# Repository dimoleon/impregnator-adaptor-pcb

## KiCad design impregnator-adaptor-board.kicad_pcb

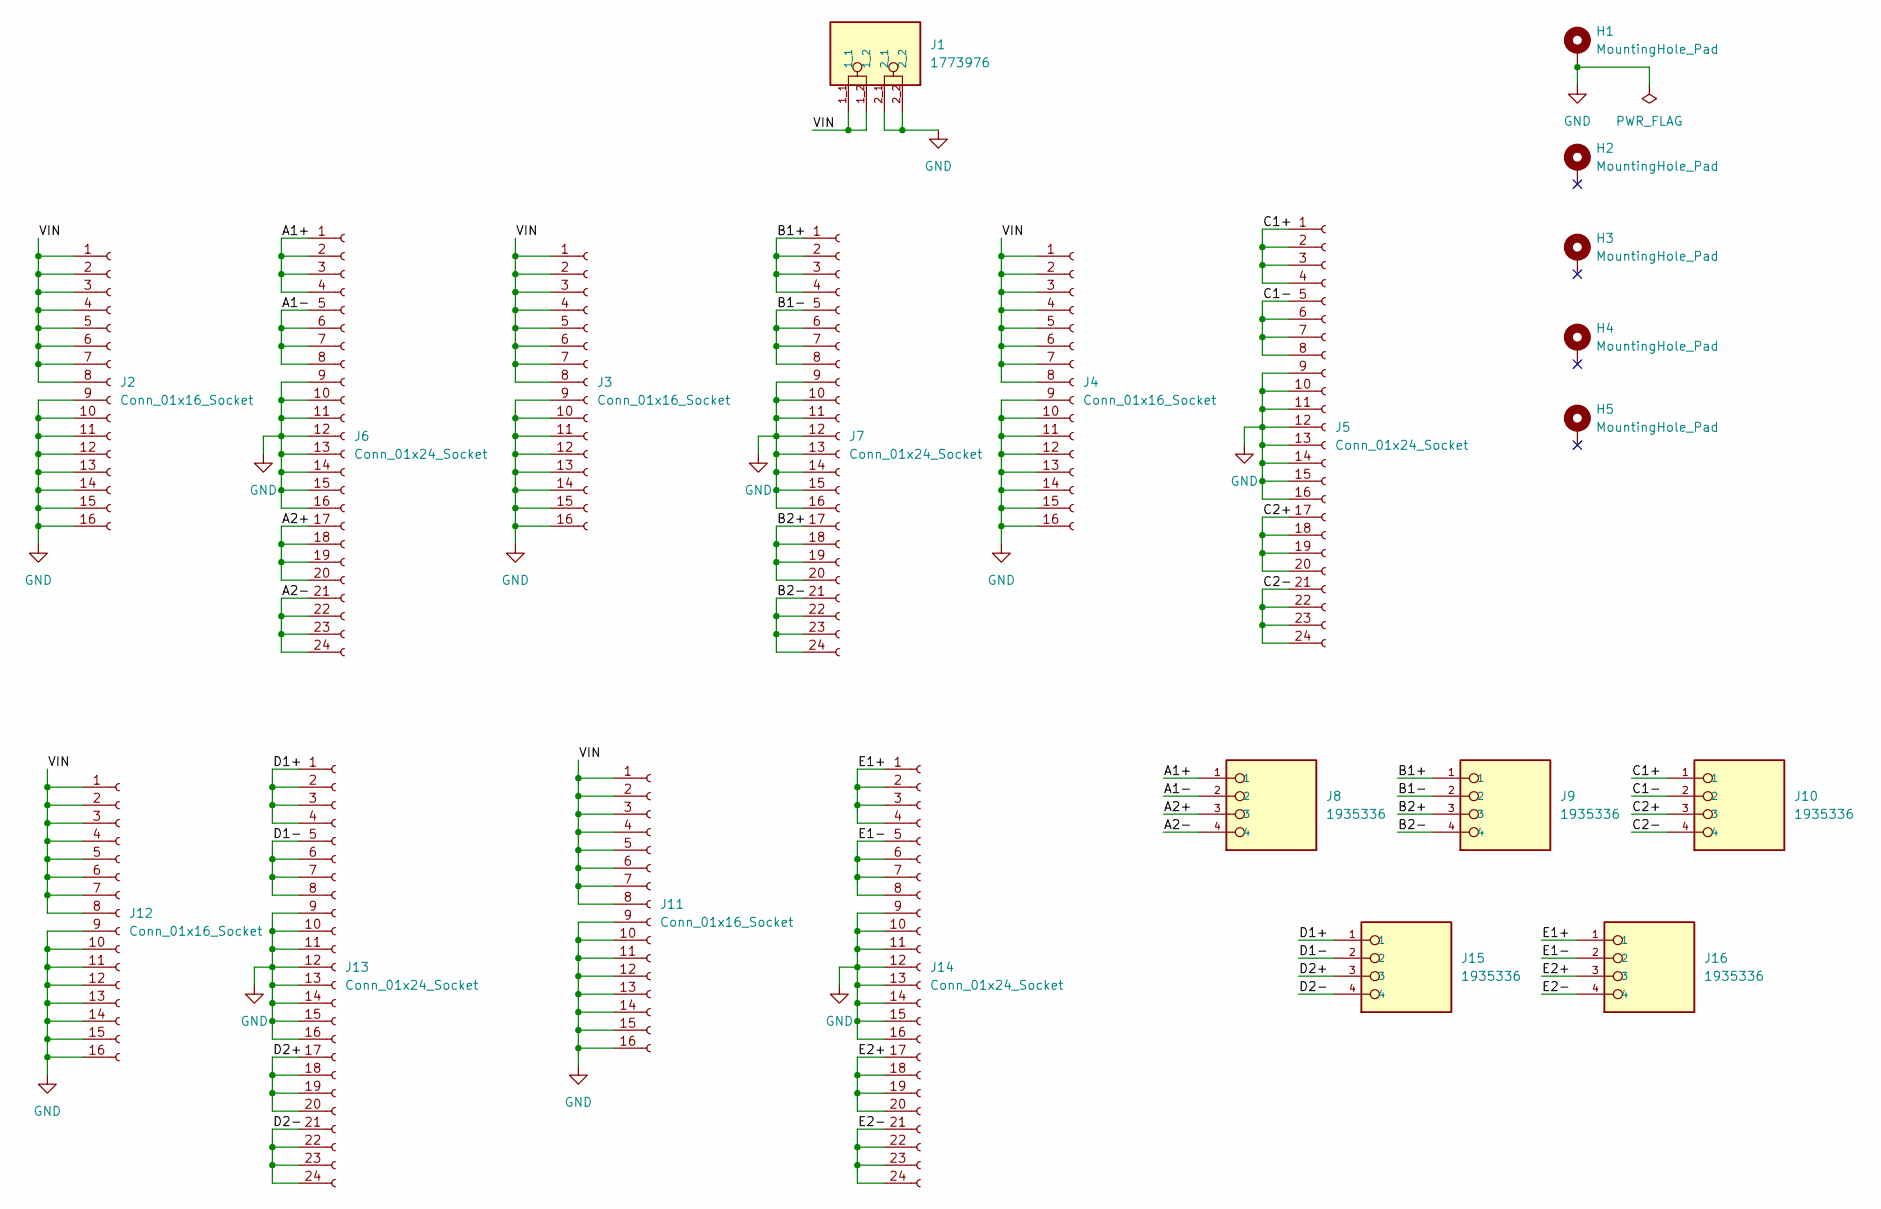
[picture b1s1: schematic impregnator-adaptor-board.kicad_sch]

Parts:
H1, H2, H3, H4, H5: MountingHole_Pad; MountingHole_3.2mm_M3_DIN965_Pad
J1: 1773976; PHOENIX_1773976; PARTREV 19.03.2015
J2, J3, J4, J11, J12: Conn_01x16_Socket; PinSocket_4x04_P2.54mm_Vertical
J5, J6, J7, J13, J14: Conn_01x24_Socket; PinSocket_2x12_P2.54mm_Vertical
J8, J9, J10, J15, J16: 1935336; PHOENIX_1935336

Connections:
/A1+: J6.1, J6.2, J6.3, J6.4, J8.1
/A1-: J6.5, J6.6, J6.7, J6.8, J8.2
/A2+: J6.17, J6.18, J6.19, J6.20, J8.3
/A2-: J6.21, J6.22, J6.23, J6.24, J8.4
/B1+: J7.1, J7.2, J7.3, J7.4, J9.1
/B1-: J7.5, J7.6, J7.7, J7.8, J9.2
/B2+: J7.17, J7.18, J7.19, J7.20, J9.3
/B2-: J7.21, J7.22, J7.23, J7.24, J9.4
/C1+: J5.1, J5.2, J5.3, J5.4, J10.1
/C1-: J5.5, J5.6, J5.7, J5.8, J10.2
/C2+: J5.17, J5.18, J5.19, J5.20, J10.3
/C2-: J5.21, J5.22, J5.23, J5.24, J10.4
/D1+: J13.1, J13.2, J13.3, J13.4, J15.1
/D1-: J13.5, J13.6, J13.7, J13.8, J15.2
/D2+: J13.17, J13.18, J13.19, J13.20, J15.3
/D2-: J13.21, J13.22, J13.23, J13.24, J15.4
/E1+: J14.1, J14.2, J14.3, J14.4, J16.1
/E1-: J14.5, J14.6, J14.7, J14.8, J16.2
/E2+: J14.17, J14.18, J14.19, J14.20, J16.3
/E2-: J14.21, J14.22, J14.23, J14.24, J16.4
/VIN: J1.1_1, J1.1_2, J2.1, J2.2, J2.3, J2.4, J2.5, J2.6, J2.7, J2.8, J3.1, J3.2, J3.3, J3.4, J3.5, J3.6, J3.7, J3.8, J4.1, J4.2, J4.3, J4.4, J4.5, J4.6, J4.7, J4.8, J11.1, J11.2, J11.3, J11.4, J11.5, J11.6, J11.7, J11.8, J12.1, J12.2, J12.3, J12.4, J12.5, J12.6, J12.7, J12.8
GND: H1.1, J1.2_1, J1.2_2, J2.9, J2.10, J2.11, J2.12, J2.13, J2.14, J2.15, J2.16, J3.9, J3.10, J3.11, J3.12, J3.13, J3.14, J3.15, J3.16, J4.9, J4.10, J4.11, J4.12, J4.13, J4.14, J4.15, J4.16, J5.9, J5.10, J5.11, J5.12, J5.13, J5.14, J5.15, J5.16, J6.9, J6.10, J6.11, J6.12, J6.13, J6.14, J6.15, J6.16, J7.9, J7.10, J7.11, J7.12, J7.13, J7.14, J7.15, J7.16, J11.9, J11.10, J11.11, J11.12, J11.13, J11.14, J11.15, J11.16, J12.9, J12.10, J12.11, J12.12, J12.13, J12.14, J12.15, J12.16, J13.9, J13.10, J13.11, J13.12, J13.13, J13.14, J13.15, J13.16, J14.9, J14.10, J14.11, J14.12, J14.13, J14.14, J14.15, J14.16

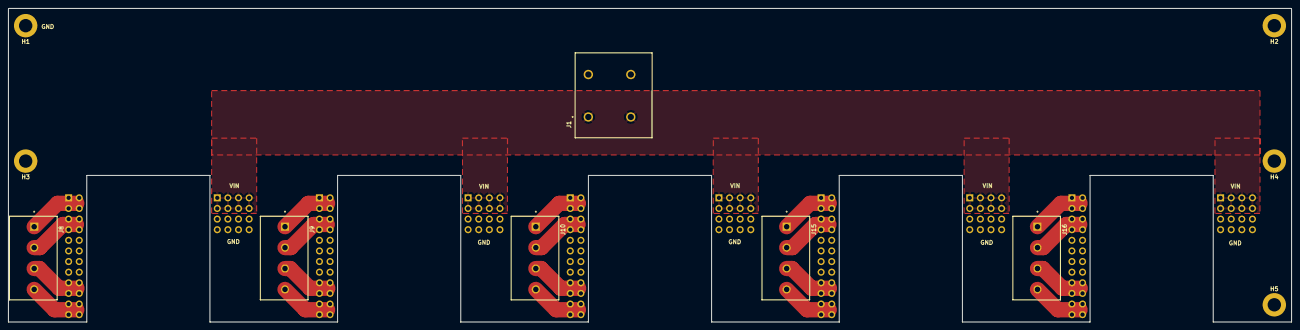
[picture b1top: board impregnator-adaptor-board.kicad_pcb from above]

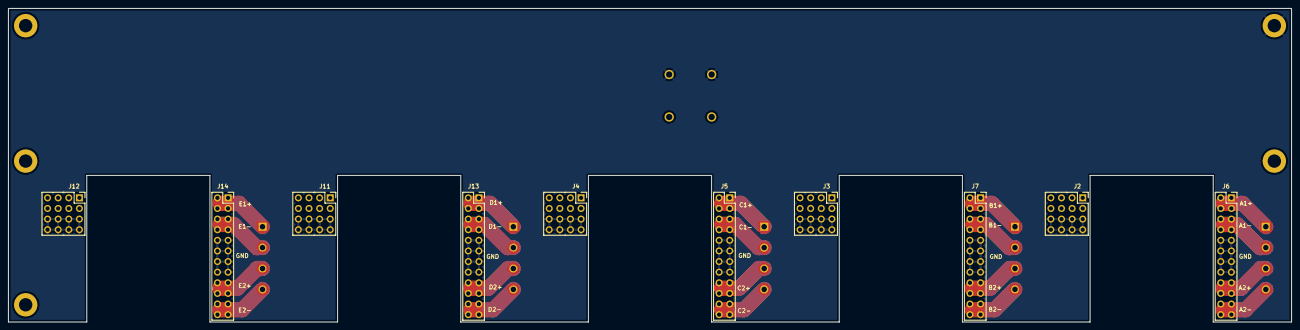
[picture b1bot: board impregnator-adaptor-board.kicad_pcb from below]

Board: 2 copper layers, 306.9 x 75.0 mm, 21 parts (10 on the bottom side), 22 nets.

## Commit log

2025-04-28 first iteration
2025-04-28 project native components
2025-04-28 remove redundant dirs
2025-04-29 use smaller central screw connector
2025-04-29 add 3d models
2025-04-30 freeze v0.1
2025-05-06 put all slots on the same side and add silkscreen
